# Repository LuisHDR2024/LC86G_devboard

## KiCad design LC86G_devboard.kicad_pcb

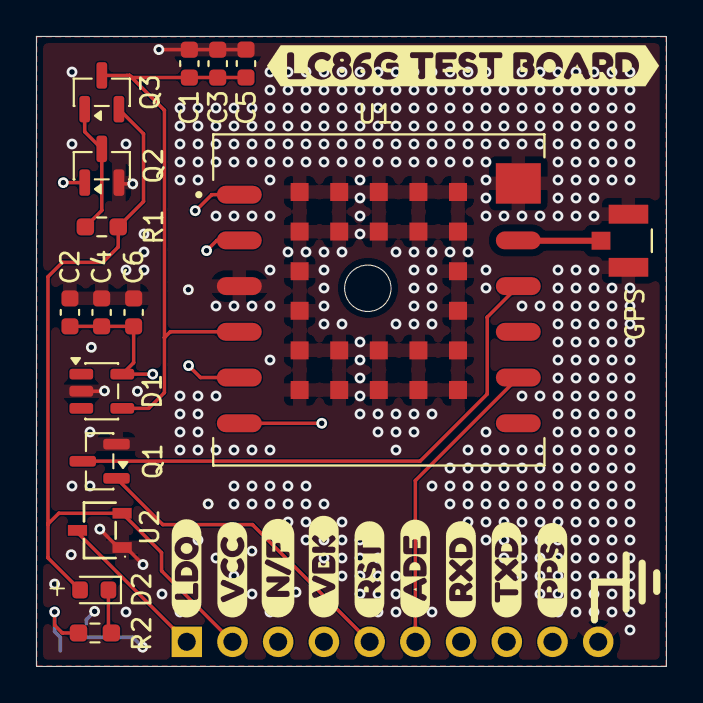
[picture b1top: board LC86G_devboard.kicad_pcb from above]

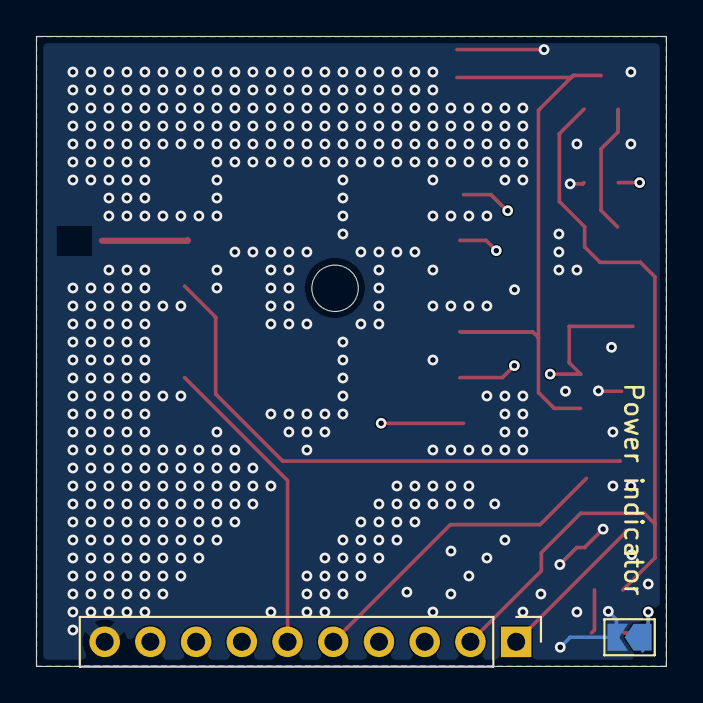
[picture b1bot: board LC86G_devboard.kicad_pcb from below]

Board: 4 copper layers, 35.0 x 35.0 mm, 28 parts (2 on the bottom side), 16 nets.

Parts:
C1, C2: 33pF; C_0603_1608Metric
C3, C4: 100nF; C_0603_1608Metric
C5: 10uF; C_0603_1608Metric
C6: 4.7uF; C_0603_1608Metric
D1: ESDA6V1SC5; SOT-23-5
D2: LED_Small; LED_0603_1608Metric
J2: U.FL-R-SMT_10_; U.FL-R-SMT_10_-foot
J3: Conn_01x10_Pin; PinHeader_1x10_P2.54mm_Vertical
Power indicator: SolderJumper_2_Open; SolderJumper-2_P1.3mm_Open_TrianglePad1.0x1.5mm
Q1, Q2: DTC143Z; SOT-23
Q3: AO3415; SOT-23
R1: 10k; R_0603_1608Metric_Pad0.98x0.95mm_HandSolder
R2: 4.7k; R_0603_1608Metric_Pad0.98x0.95mm_HandSolder
U1: LC86G; XCVR_LC86G
U2: XC6206P332MR; SOT-23-3_L2.9-W1.6-P1.90-LS2.8-BR
kibuzzard-6A1C8FBC: G***; kibuzzard-6A1C8FBC
kibuzzard-6A7817EE: G***; kibuzzard-6A7817EE
kibuzzard-6A78181D: G***; kibuzzard-6A78181D
kibuzzard-6A78183E: G***; kibuzzard-6A78183E
kibuzzard-6A78187E: G***; kibuzzard-6A78187E
kibuzzard-6A781809: G***; kibuzzard-6A781809
kibuzzard-6A781813: G***; kibuzzard-6A781813
kibuzzard-6A781856: G***; kibuzzard-6A781856
kibuzzard-6A781867: G***; kibuzzard-6A781867
kibuzzard-6A781898: G***; kibuzzard-6A781898

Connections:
/GPIO.RESET: J3.5, Q1.1 (B)
/LC86G.1PPS: J3.9, U1.6 (1PPS)
/LC86G.AADET: J3.6, U1.8 (~AADET)
/LC86G.EX_ANT: J2.SIG, U1.11 (EX_ANT)
/LC86G.RESET: Q1.3 (C), U1.10 (~RESET)
/LC86G.RXD: J3.7, U1.1 (RXD)
/LC86G.TXD: J3.8, U1.2 (TXD)
/LC86G.VCC: C1.1, C3.1, C5.1, D1.4 (K), Q3.3 (D), U1.4 (VCC)
/LC86G.V_BCKP: C2.1, C4.1, C6.1, D1.5 (K), J3.4, U1.5 (V_BCKP)
/LDO: J3.1, U2.3 (Vin)
/ON/OFF: J3.3, Q2.1 (B)
/VCC: D2.2 (A), J3.2, Q3.2 (S), R1.1, U2.2 (Vout)
GND: C1.2, C2.2, C3.2, C4.2, C5.2, C6.2, D1.2 (A), J2.G1, J2.G2, J3.10, Power indicator.2 (B), Q1.2 (E), Q2.2 (E), U1.3 (GND), U1.12 (GND), U1.13 (GND), U1.14 (GND), U1.15 (GND), U1.16 (GND), U1.17 (GND), U1.18 (GND), U1.19 (GND), U1.20 (GND), U1.21 (GND), U1.22 (GND), U1.23 (GND), U1.24 (GND), U1.25 (GND), U1.26 (GND), U1.27 (GND), U1.28 (GND), U1.29 (GND), U1.30 (GND), U1.31 (GND), U1.32 (GND), U1.33 (GND), U1.34 (GND), U1.35 (GND), U1.36 (GND), U2.1 (GND)
unnamed: D2.1 (K), R2.1
unnamed: Power indicator.1 (A), R2.2
unnamed: Q2.3 (C), Q3.1 (G), R1.2

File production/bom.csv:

Designator,Footprint,Quantity,Value,LCSC Part #
"C1, C2",0603,2,33pF,
"C3, C4",0603,2,100nF,
C5,0603,1,10uF,
C6,0603,1,4.7uF,
D1,SOT-23-5,1,ESDA6V1SC5,
J1,PinHeader_1x09_P2.54mm_Vertical,1,Conn_01x09_Pin,
J2,U.FL-R-SMT_10_-foot,1,U.FL-R-SMT_10_,
"Q1, Q2",SOT-23,2,DTC143Z,
Q3,SOT-23,1,AO3415,
R1,0603,1,10k,
U1,XCVR_LC86G,1,LC86G,

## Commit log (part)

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2026-02-12 primer commit v1.0
2026-02-12 correxion de nombre de proyecto
2026-05-16 pistas faltantes ruteadas
2026-06-05 carga final
